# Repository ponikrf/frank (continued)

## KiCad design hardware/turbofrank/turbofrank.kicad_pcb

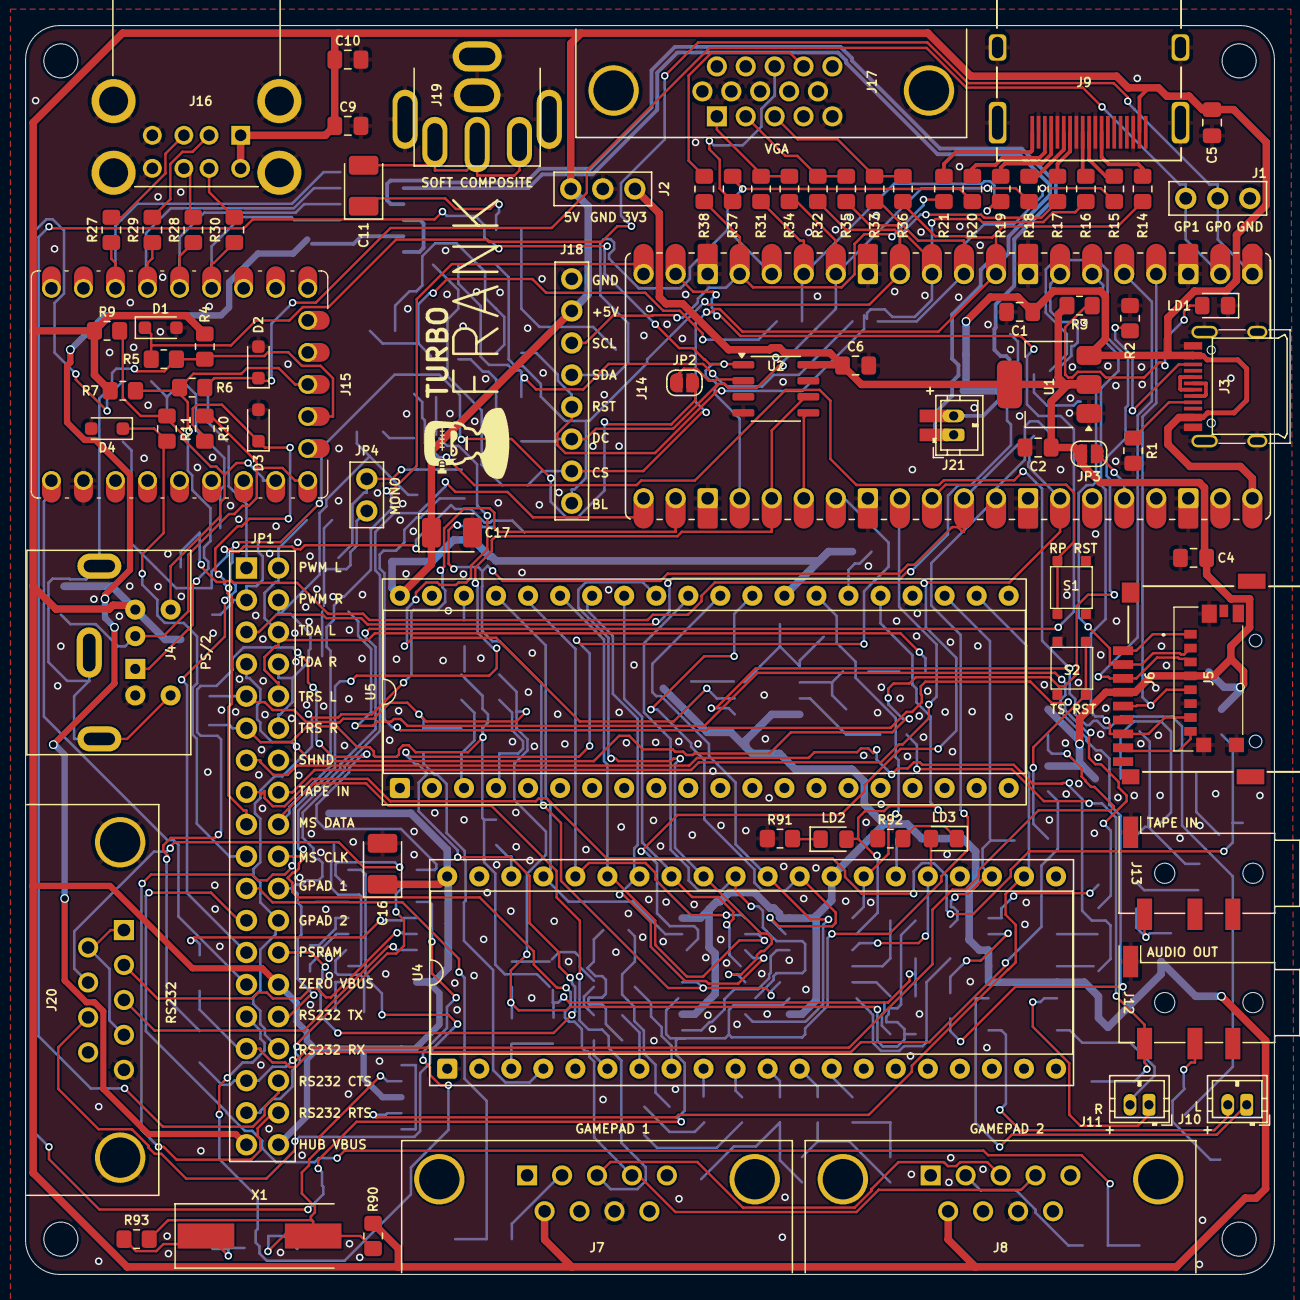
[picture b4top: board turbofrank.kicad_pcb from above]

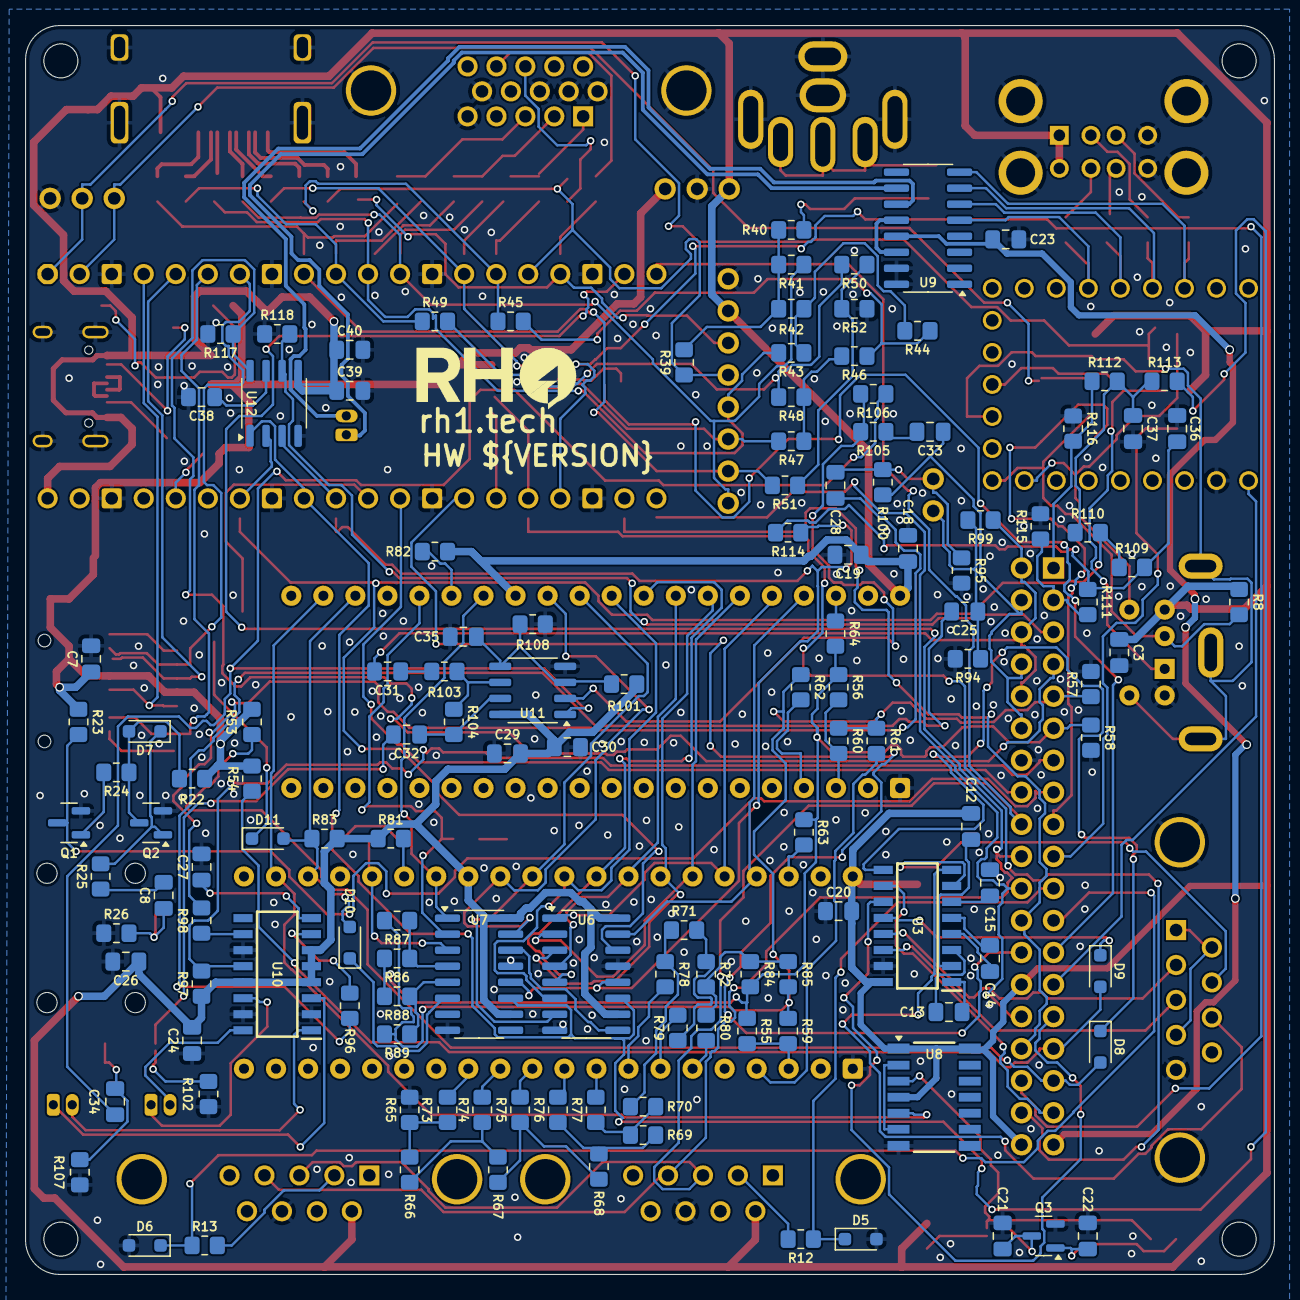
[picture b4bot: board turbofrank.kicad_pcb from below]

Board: 2 copper layers, 99.0 x 99.0 mm, 219 parts (132 on the bottom side), 187 nets.

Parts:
C1, C2, C9, C10, C29, C31, C32, C33, C34, C35, C38, C39: 10u; Capacitor (0805)
C3, C4, C5, C6, C7, C8, C18, C19, C20, C27, C30, C40: 100n; Capacitor (0805)
C11: 220u; Capacitor (3528, tantalum, polar)
C12, C13, C14, C15, C24, C25, C28: 1u; Capacitor (0805)
C16, C17: 100u; Capacitor (3528, tantalum, polar)
C21, C22: 22p; Capacitor (0805)
C23: 4.7u; Capacitor (0805)
C26: 47u; Capacitor (0805)
C36, C37: 47n; Capacitor (0805)
D1, D2, D3, D4, D5, D6: 3V3; Diode (SOD-323)
D7, D8, D9, D10, D11: 1N4148; Diode (SOD-323)
H1, H2, H3, H4: Hole 2.7mm; Mounting Hole (2.7mm)
J1: UART; Pin Header (1x03)
J2: PWR; Pin Header (1x03)
J3: USB4215; USB Type C
J4: MDC-036; MiniDIN (6 Pin, female)
J5: 0475710001; MicroSD (SMD, short)
J6: 104031-0811; MicroSD (SMD, long)
J7, J8, J20: D-SUB 9 Male; D-SUB (9 pin, male, top mount)
J9: DC3RX19JA2; HDMI (female)
J10: PAM L; Connector Female ZH 1.50mm (2 pins)
J11: PAM R; Connector Female ZH 1.50mm (2 pins)
J12, J13: PJ-320D; Jack (3.5mm, PJ-320D)
J14: Rasberry Pi Pico; Raspberry Pi Pico
J15: RP2040-Zero; Raspberry Pi Zero
J16: SS-52100-004; USB Type A (stacked)
J17: D-SUB 15 Female; D-SUB (15 pin, female)
J18: Pin Header 1x08; Pin Header (1x08)
J19: RCA-103; RCA
J21: USB HUB Data; Connector Female ZH 1.50mm (2 pins + tracks)
JP1: Main Jumper Set; Pin Header (2x19)
JP2, JP3: Jumper (Solder); Jumper (solder)
JP4: Mono; Pin Header (1x02)
LD1: Green; LED (0805)
LD2, LD3: Orange; LED (0805)
Q1, Q2, Q3: BC850; SOT-23
R1, R2: 5.1K; Resistor (0805)
R3, R4, R7, R8, R9, R12, R13, R23, R34, R35, R36, R53, R54, R66, R67, R68, R69, R70, R71, R72, R81, R82, R90, R91, R92, R113, R114: 1K; Resistor (0805)
R5, R6, R10, R11, R26, R37, R38: 100R; Resistor (0805)
R14, R15, R16, R17, R18, R19, R20, R21, R41, R43, R45, R47, R49, R51: 270R; Resistor (0805)
R22, R24, R25, R83, R84, R85, R86, R87, R88, R89, R96, R97, R98, R99, R100, R101, R103, R105, R108, R111, R112: 10K; Resistor (0805)
R27, R28, R29, R30: 22R; Resistor (0805)
R31, R32, R33: 330R; Resistor (0805)
R39: 750R; Resistor (0805)
R40: 51R; Resistor (0805)
R42, R44, R46, R48, R50: 150R; Resistor (0805)
R52: 300R; Resistor (0805)
R55, R56, R61, R62, R65, R73, R74, R75, R76, R77, R78, R79, R80, R94, R95, R109, R110, R115, R116: 2K; Resistor (0805)
R57, R58: 120R; Resistor (0805)
R59, R60, R63, R64: 4.7K; Resistor (0805)
R93: 100K; Resistor (0805)
R102, R107: 20K; Resistor (0805)
R104, R106: 47K; Resistor (0805)
R117, R118: 470R; Resistor (0805)
S1: TS-1233; Button (SMD, 3x3mm, 1-1)
S2: KLS7-TS3302; Button (SMD, 3x3mm, 1-1)
U1: NCP1117 3.3; SOT-223
U2: ESP-PSRAM32; SO-8
U3: MAX232CSE+; SOIC127P600X175-16N
U4, U5: JFC95101; DIP-40 (Socket)
U6, U7: 74HC595; SOP-16
U8: 74HC74; 74HCT74D
U9: MW7211A; SOP-16
U10: PAM8403D; SOIC127P600X175-16N
U11: LM358; SO-8
U12: TDA1387T; SO-8
X1: 3.58 MHz; Crystal (HC49-S)

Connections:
+3V3: C2.1, C4.2, C6.1, C7.1, J2.1, J5.P4 (VDD), J6.4 (VDD), JP3.2 (B), R3.2, R22.1, R23.1, R53.2, R54.2, U1.2 (VO), U2.8 (VCC)
/AMP_IN_L: C31.1, JP1.2, JP1.6, JP1.10, R99.1
/AMP_IN_R: C33.1, JP1.4, JP1.8, JP1.12, R100.1
/Audio Out/AMP_OUTL: C32.2, J12.T, R102.2
/Audio Out/AMP_OUTR: C34.2, J12.R, R107.2
/Audio Out/AMP_PAM_OUTL_M: J10.2, U10.3 (-OUTL)
/Audio Out/AMP_PAM_OUTL_P: J10.1, U10.1 (+OUT_L)
/Audio Out/AMP_PAM_OUTR_M: J11.2, U10.14 (-OUT_R)
/Audio Out/AMP_PAM_OUTR_P: J11.1, U10.16 (+OUT_R)
/Audio Out/Amplifier/ MONO_L: C25.1, JP4.1, R94.1, R99.2
/Audio Out/Amplifier/MONO_R: C28.1, JP4.2, R95.1, R100.2
/Audio Out/TS/A1: R62.2, U5.4 (B)
/Audio Out/TS/A2: R61.2, U4.4 (B)
/Audio Out/TS/B1: R56.2, R60.2, U5.3 (A)
/Audio Out/TS/B2: R55.2, R59.2, U4.3 (A)
/Audio Out/TS/BEEP: R86.2, R87.2, U7.4 (QE)
/Audio Out/TS/C1: R64.2, U5.38 (C)
/Audio Out/TS/C2: R63.2, U4.38 (C)
/Audio Out/TS/CLK_1.75M: U4.22 (CLOCK), U5.22 (CLOCK), U8.5 (Q)
/Audio Out/TS/COVOX_OUT: R72.2, R80.1, R84.2, R85.2
/Audio Out/TS/DA0: U4.37 (DA0), U5.37 (DA0), U6.15 (QA)
/Audio Out/TS/DA1: U4.36 (DA1), U5.36 (DA1), U6.1 (QB)
/Audio Out/TS/DA2: U4.35 (DA2), U5.35 (DA2), U6.2 (QC)
/Audio Out/TS/DA3: U4.34 (DA3), U5.34 (DA3), U6.3 (QD)
/Audio Out/TS/DA4: U4.33 (DA4), U5.33 (DA4), U6.4 (QE)
/Audio Out/TS/DA5: U4.32 (DA5), U5.32 (DA5), U6.5 (QF)
/Audio Out/TS/DA6: U4.31 (DA6), U5.31 (DA6), U6.6 (QG)
/Audio Out/TS/DA7: U4.30 (DA7), U5.30 (DA7), U6.7 (QH)
/Audio Out/TS/DAC0: R73.2, U4.13 (IOB0)
/Audio Out/TS/DAC1: R74.2, U4.12 (IOB1)
/Audio Out/TS/DAC2: R75.2, U4.11 (IOB2)
/Audio Out/TS/DAC3: R76.2, U4.10 (IOB3)
/Audio Out/TS/DAC4: R77.2, U4.9 (IOB4)
/Audio Out/TS/DAC5: R78.2, U4.8 (IOB5)
/Audio Out/TS/DAC6: R79.2, U4.7 (IOB6)
/Audio Out/TS/DAC7: R80.2, U4.6 (IOB7)
/Audio Out/TS/SAVE: R88.2, R89.2, U7.5 (QF)
/Audio Out/TS/YM_BC1: U4.29 (BC1), U5.29 (BC1), U7.15 (QA)
/Audio Out/TS/YM_BDIR: U4.27 (BDIR), U5.27 (BDIR), U7.1 (QB)
/Audio Out/TS/YM_CS1: LD2.2 (A), U5.25 (A8), U7.2 (QC)
/Audio Out/TS/YM_CS2: LD3.2 (A), U4.25 (A8), U7.3 (QD)
/Audio Out/TS/YM_RST: D10.2 (A), D11.2 (A), R83.1, U4.23 (~RESET), U5.23 (~RESET)
/Audio Out/TS/YM_SEL1: R82.2, U5.26 (~SEL)
/Audio Out/TS/YM_SEL2: R81.2, U4.26 (~SEL)
/Composite/CVBS: C11.2, J19.1
/GP1_DATA: D5.1 (K), JP1.21, R12.1
/GP2_DATA: D6.1 (K), JP1.23, R13.1
/GPIO0: D1.1 (K), J1.2, J14.1 (GPIO0), R5.2
/GPIO1: D2.1 (K), J1.3, J14.2 (GPIO1), R6.2
/GPIO2: J5.P5 (CLK), J6.5 (CLK), J14.4 (GPIO2)
/GPIO3: J5.P3 (CMD), J6.3 (CMD), J14.5 (GPIO3)
/GPIO4: J5.P7 (DAT0), J6.7 (DAT0), J14.6 (GPIO4)
/GPIO5: J5.P2 (CD/DAT3), J6.2 (DAT3/CD), J14.7 (GPIO5)
/GPIO6: J14.9 (GPIO6), J18.7, R14.2, R36.1, R51.1
/GPIO7: J14.10 (GPIO7), R15.2, R33.1, R49.1
/GPIO8: J14.11 (GPIO8), J18.5, R16.2, R35.1, R43.1
/GPIO9: J14.12 (GPIO9), J18.8, R17.2, R32.1, R41.1
/GPIO10: J14.14 (GPIO10), J18.6, R18.2, R34.1, R47.1
/GPIO11: J14.15 (GPIO11), R19.2, R31.1, R45.1
/GPIO12: J14.16 (GPIO12), J18.4, R20.2, R37.2, R39.1
/GPIO13: J14.17 (GPIO13), J18.3, R21.2, R38.2
/GPIO14: J7.4, J8.4, J14.19 (GPIO14), JP1.20
/GPIO15: J7.3, J8.3, J14.20 (GPIO15), JP1.18
/GPIO16: J14.21 (GPIO16), JP1.22, JP1.30
/GPIO17: J14.22 (GPIO17), JP1.24, JP1.32
/GPIO18: J14.24 (GPIO18), JP1.34, U2.1 (~CE)
/GPIO19: J14.25 (GPIO19), JP1.36, U2.6 (SCLK)
/GPIO20: J14.26 (GPIO20), U2.5 (SI/SIO)
/GPIO21: J14.27 (GPIO21), JP1.26
/GPIO22: J14.29 (GPIO22), JP1.16
/GPIO26: J14.31 (GPIO26_ADC0), R114.2, U6.12 (RCLK), U7.12 (RCLK), U12.3 (DATA)
/GPIO27: J14.32 (GPIO27_ADC1), R113.2, U6.11 (SRCLK), U7.11 (SRCLK), U12.1 (SCLK)
/GPIO28: J14.34 (GPIO28_ADC2), R109.1, R110.1, U6.14 (SER), U12.2 (LRCK)
/KB_CLK: J4.5, J15.13 (12), R4.2, R5.1
/KB_DATA: J4.1, J15.12 (11), R6.1, R7.2
/LOAD_IN_D: JP1.15, Q1.3 (C), R23.2
/MS_CLK: J4.6, J15.16 (15), R9.2, R11.1
/MS_CLK_3V: D4.1 (K), JP1.19, R11.2
/MS_DATA: J4.2, J15.15 (14), R8.2, R10.1
/MS_DATA_3V: D3.1 (K), JP1.17, R10.2
/Micro SD/DAT1: J5.P8 (DAT1), J6.8 (DAT1)
/Micro SD/DAT2: J5.P1 (DAT2), J6.1 (DAT2)
/PSR_SOSIO: JP1.25, JP2.2 (B)
/PWM_OUT_L: JP1.1, R112.2, R116.1
/PWM_OUT_R: JP1.3, R111.2, R115.1
/Power/D+: J3.6 (DP1), J3.8 (DP2)
/Power/D-: J3.5 (DN2), J3.7 (DN1)
/RS232/C1+: C13.2, U3.1 (C1+)
/RS232/C1-: C13.1, U3.3 (C1-)
/RS232/C2+: C14.2, U3.4 (C2+)
/RS232/C2-: C14.1, U3.5 (C2-)
/RS232/CTS_IN: J20.7, U3.7 (T2OUT)
/RS232/CTS_MAX: D8.1 (K), U3.9 (R2OUT)
/RS232/RTS_IN: J20.8, U3.8 (R2IN)
/RS232/RX_IN: J20.3, U3.14 (T1OUT)
/RS232/RX_MAX: D9.1 (K), U3.12 (R1OUT)
/RS232/TX_IN: J20.2, U3.13 (R1IN)
/RS232/V+: C12.1, U3.2 (V+)
/RS232/V-: C15.1, U3.6 (V-)
/RS232_CTS: D8.2 (A), JP1.33, R53.1
/RS232_RTS: JP1.35, U3.10 (T2IN)
/RS232_RX: D9.2 (A), JP1.31, R54.1
/RS232_TX: JP1.29, U3.11 (T1IN)
/RUN: J14.30 (RUN), S1.1
/SHND: JP1.13, R97.2, U10.12 (SHND)
/TDA_L: JP1.5, R118.2, U12.6 (A_LEFT)
/TDA_R: JP1.7, R117.1, U12.8 (A_RIGHT)
/TS_L: JP1.9, R57.1, R59.1, R60.1, R61.1, R62.1, R85.1, R87.1, R89.1
/TS_R: JP1.11, R55.1, R56.1, R58.1, R63.1, R64.1, R84.1, R86.1, R88.1
/USB Hub/DM_IN: J21.2, U9.10 (DMU)
/USB Hub/DP_IN: J21.1, U9.11 (DPU)
/USBH_VBUS: C23.1, JP1.37, U9.13 (VDD5)
/USB_D1M: J15.4 (3), R29.1, U9.7 (DM3)
/USB_D1P: J15.3 (2), R27.1, U9.8 (DP3)
/USB_D2M: J15.6 (5), R30.1, U9.5 (DM2)
/USB_D2P: J15.5 (4), R28.1, U9.6 (DP2)
/ZERO_VBUS: J15.23 (5V), JP1.27
GND: C1.2, C2.2, C3.2, C4.1, C5.2, C6.2, C7.2, C9.2, C10.2, C15.2, C16.2, C17.2, C18.2, C19.2, C20.2, C21.1, C22.1, C23.2, C24.2, C26.2, C27.2, C29.1, C30.1, C35.1, C36.2, C37.2, C38.2, C39.2, C40.2, D1.2 (A), D2.2 (A), D3.2 (A), D4.2 (A), D5.2 (A), D6.2 (A), J1.1, J2.2, J3.1 (GND), J3.12 (GND), J3.13 (SHIELD), J4.3, J5.G1 (GND_1), J5.G2 (GND_2), J5.G3 (GND_3), J5.P6 (VSS), J6.6 (VSS), J7.8, J8.8, J9.2 (G_D2), J9.5 (G_D1), J9.8 (G_D0), J9.11 (G_CLK), J9.17 (G_DDC/CEC), J9.20 (SHIELD1), J9.21 (SHIELD2), J9.22 (SHIELD3), J9.23 (SHIELD4), J12.S, J13.S, J14.3 (GND), J14.8 (GND), J14.13 (GND), J14.18 (GND), J14.23 (GND), J14.28 (GND), J14.33 (AGND), J14.38 (GND), J15.22 (GND), J16.4 (GND1), J16.8 (GND2), J16.9 (Shield), J17.0, J17.5, J17.6, J17.7, J17.8, J17.10, J18.1, J19.2, J20.5, JP1.14, LD1.1 (K), Q1.2 (E), Q2.2 (E), Q3.2 (E), R1.1, R2.1, R26.2, R52.1, R57.2, R58.2, R65.1, R91.1, R92.1, R94.2, R95.2, R102.1, R107.1, R108.1, R115.2, R116.2, R117.2, R118.1, S1.2, S2.2, U1.1 (GND), U2.4 (VSS), U3.15 (GND), U4.1 (VSS), U4.24 (~A9), U5.1 (VSS), U5.24 (~A9), U6.8 (GND), U6.13 (~OE), U7.8 (GND), U7.13 (~OE), U8.7 (GND), U9.15 (GND), U9.16 (GND), U10.2 (PGND), U10.11 (GND), U10.15 (PGND), U11.4 (V-), U12.4 (AGND)
unnamed: C8.1, J13.T, R26.1
unnamed: C8.2, R25.1
unnamed: C11.1, R40.2
unnamed: C25.2, R96.2
unnamed: C28.2, R98.2
unnamed: C31.2, R103.2
unnamed: C32.1, R104.1, U11.7
unnamed: C33.2, R105.2
unnamed: C34.1, R106.1, U11.1
unnamed: C36.1, R109.2, R111.1, R114.1
unnamed: C37.1, R110.2, R112.1, R113.1
unnamed: D7.2 (A), Q2.3 (C), R22.2, R24.1
unnamed: D7.1 (K), Q2.1 (B), R25.2
unnamed: D10.1 (K), U7.6 (QG)
unnamed: D11.1 (K), S2.1
unnamed: J3.4 (CC1), R1.2
unnamed: J3.10 (CC2), R2.2
unnamed: J7.2, R12.2
unnamed: J8.2, R13.2
unnamed: J9.12 (CLKN), R14.1
unnamed: J9.10 (CLKP), R15.1
unnamed: J9.9 (D0N), R16.1
unnamed: J9.7 (D0P), R17.1
unnamed: J9.6 (D1N), R18.1
unnamed: J9.4 (D1P), R19.1
unnamed: J9.3 (D2N), R20.1
unnamed: J9.1 (D2P), R21.1
unnamed: J14.36 (3V3), JP3.1 (A)
unnamed: J16.3 (D1+), R27.2
unnamed: J16.2 (D1-), R29.2
unnamed: J16.7 (D2+), R28.2
unnamed: J16.6 (D2-), R30.2
unnamed: J17.1, R31.2, R34.2
unnamed: J17.2, R32.2, R35.2
unnamed: J17.3, R33.2, R36.2
unnamed: J17.13, R37.1
unnamed: J17.14, R38.1
unnamed: J20.1, J20.4, J20.6
unnamed: JP2.1 (A), U2.2 (SO/SIO)
unnamed: LD1.2 (A), R3.1
unnamed: LD2.1 (K), R91.2
unnamed: LD3.1 (K), R92.2
unnamed: Q1.1 (B), R24.2
unnamed: C22.2, Q3.1 (B), R93.1, X1.1
unnamed: C21.2, Q3.3 (C), R90.1, R93.2, U8.3 (C), X1.2
unnamed: R39.2, R40.1, R41.2, R42.2
unnamed: R42.1, R43.2, R44.2
unnamed: R44.1, R45.2, R46.2
unnamed: R46.1, R47.2, R48.2
unnamed: R48.1, R49.2, R50.2
unnamed: R50.1, R51.2, R52.2
unnamed: R65.2, R66.1, R73.1
unnamed: R66.2, R67.1, R74.1
unnamed: R67.2, R68.1, R75.1
unnamed: R68.2, R69.1, R76.1
unnamed: R69.2, R70.1, R77.1
unnamed: R70.2, R71.1, R78.1
unnamed: R71.2, R72.1, R79.1
unnamed: U6.9 (QH'), U7.14 (SER)
unnamed: U8.2 (D), U8.6 (~Q)
unnamed: U9.12 (VD33), U9.14 (VD3)
unnamed: R96.1, U10.7 (INL)
unnamed: R98.1, U10.10 (INR)
unnamed: C27.1, U10.8 (VREF)
unnamed: C35.2, R101.1, R108.2, U11.3 (+), U11.5 (+)
unnamed: R105.1, R106.2, U11.2 (-)
unnamed: R103.1, R104.2, U11.6 (-)
unnamed: C38.1, U12.7 (FLT)
VBUS: C1.1, C3.1, C5.1, C9.1, C10.1, C12.2, C16.1, C17.1, C18.1, C19.1, C20.1, C24.1, C26.1, C29.2, C30.2, C39.1, C40.1, J2.3, J3.2 (VBUS), J3.11 (VBUS), J4.4, J7.6, J8.6, J9.18 (+5V), J14.40 (VBUS), J16.1 (VBUS1), J16.5 (VBUS2), J18.2, JP1.28, JP1.38, R4.1, R7.1, R8.1, R9.1, R81.1, R82.1, R83.2, R90.2, R97.1, R101.2, U1.3 (VI), U3.16 (VCC), U4.28 (BC2), U4.40 (VCC), U5.28 (BC2), U5.40 (VCC), U6.10 (~SRCLR), U6.16 (VCC), U7.10 (~SRCLR), U7.16 (VCC), U8.1 (~R), U8.4 (~S), U8.14 (VCC), U10.4 (PVDD), U10.5 (MUTE), U10.6 (VDD), U10.13 (PVDD), U11.8 (V+), U12.5 (VA)

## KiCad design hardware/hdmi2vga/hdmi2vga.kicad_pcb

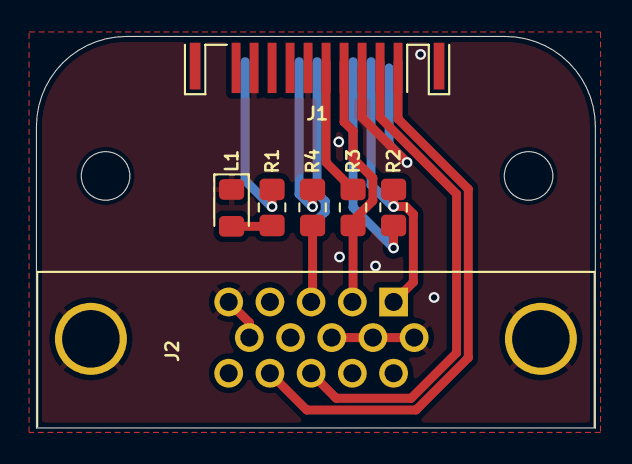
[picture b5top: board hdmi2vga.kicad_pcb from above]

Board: 2 copper layers, 31.1 x 21.8 mm, 9 parts (0 on the bottom side), 11 nets.

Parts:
H1, H2: MountingHole; Mounting Hole (2.7mm)
J1: HDMI; HDMI (male)
J2: VGA; D-SUB (15 pin, female)
L1: HDMI LED; LED (0805)
R1: 1K; Resistor (0805)
R2, R3, R4: 820R; Resistor (0805)

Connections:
/CLKN_VGA_B: J1.12 (CLKN), R4.1
/CLKP_VGA_BH: J1.10 (CLKP), J2.3, R4.2
/D0N_VGA_G: J1.9 (D0N), R3.1
/D0P_VGA_GH: J1.7 (D0P), J2.2, R3.2
/D1N_VGA_R: J1.6 (D1N), R2.1
/D1P_VGA_RH: J1.4 (D1P), J2.1, R2.2
/D2N_VGA_HS: J1.3 (D2N), J2.13
/D2P_VGA_VS: J1.1 (D2P), J2.14
GND: J1.2 (G_D2), J1.5 (G_D1), J1.8 (G_D0), J1.11 (G_CLK), J1.17 (G_DDC/CEC), J2.0, J2.5, J2.6, J2.7, J2.8, J2.10, L1.1 (K)
unnamed: J1.18 (+5V), R1.1
unnamed: L1.2 (A), R1.2

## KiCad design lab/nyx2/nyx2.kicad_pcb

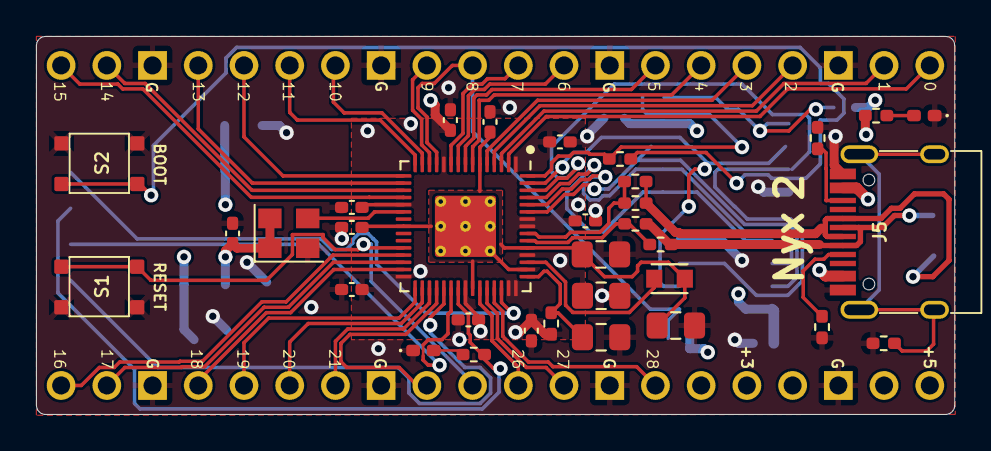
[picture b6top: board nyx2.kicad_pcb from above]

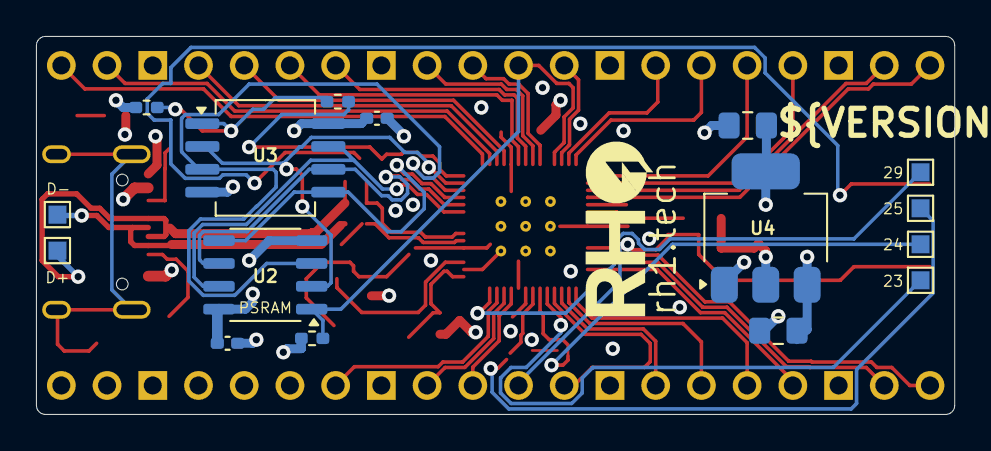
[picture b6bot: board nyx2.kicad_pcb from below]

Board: 4 copper layers, 51.0 x 21.0 mm, 47 parts (12 on the bottom side), 55 nets.

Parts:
C1, C3, C4, C5, C6, C7, C8, C9, C10, C11, C15, C16: 100n; Capacitor (0402)
C2, C12, C13, C14: 4.7u; Capacitor (0805)
C17, C18: 10u; Capacitor (0805)
J1: CON_PICO_21-40
J2: CON_PICO_1-20
J3: Test Points (1mm x 5)
J4: Test Points (1mm x 2)
J5: USB4215-03-A; USB Type C
L1: 3.3u; IND_LQH2MCN100K02L
LD1: Blue; LED (0402)
LD2: Green; LED (0402)
R1, R4: 150R; Resistor (0402)
R2: 33; Resistor (0402)
R3, R5: 33R; Resistor (0402)
R6, R10, R12: 1K; Resistor (0402)
R7, R8: 10K; Resistor (0402)
R9: 0R; Resistor (0402)
R11, R13: 5.1K; Resistor (0402)
R14: 1M; Resistor (0402)
S1: Reset; Button (SMD, 3x3mm, 1-1)
S2: TS-1233; Button (SMD, 3x3mm, 1-1)
U1: RP2350; QFN 60 (RP2350A)
U2: ESP-PSRAM32; SO-8
U3: W25Q128JVS; SOIC-8
U4: NCP1117 3.3; SOT-223
Y1: ASE-12MHz; Crystal (3225, active)

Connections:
+1V1: C1.1, C2.1, C3.1, C14.1, L1.1, U1.6 (DVDD), U1.23 (DVDD), U1.39 (DVDD), U1.50 (VREG_FB)
+3V3: C4.1, C5.1, C6.1, C7.1, C8.1, C9.1, C10.1, C11.1, C13.1, C15.1, C16.1, C18.1, J1.36, R2.1, R7.2, R8.1, R12.2, U1.1 (IOVDD), U1.11 (IOVDD), U1.20 (IOVDD), U1.30 (IOVDD), U1.38 (IOVDD), U1.44 (ADC_AVDD), U1.45 (IOVDD), U1.49 (VREG_VIN), U1.53 (USB_OTP_VDD), U1.54 (QSPI_IOVDD), U2.8 (VCC), U3.8 (VCC), U4.2 (VO), Y1.1 (EN), Y1.4 (Vdd)
/D+: J4.1, J5.6 (DP1), J5.8 (DP2), R1.1, R3.1
/D-: J4.2, J5.5 (DN2), J5.7 (DN1), R4.1, R5.1
/GPIO0: J2.1, U1.2 (GPIO0)
/GPIO1: J2.2, U1.3 (GPIO1)
/GPIO2: J2.4, U1.4 (GPIO2)
/GPIO3: J2.5, U1.5 (GPIO3)
/GPIO4: J2.6, U1.7 (GPIO4)
/GPIO5: J2.7, U1.8 (GPIO5)
/GPIO6: J2.9, U1.9 (GPIO6)
/GPIO7: J2.10, U1.10 (GPIO7)
/GPIO8: J2.11, R7.1, U1.12 (GPIO8), U2.1 (~CE)
/GPIO9: J2.12, U1.13 (GPIO9)
/GPIO10: J2.14, U1.14 (GPIO10)
/GPIO11: J2.15, U1.15 (GPIO11)
/GPIO12: J2.16, U1.16 (GPIO12)
/GPIO13: J2.17, U1.17 (GPIO13)
/GPIO14: J2.19, U1.18 (GPIO14)
/GPIO15: J2.20, U1.19 (GPIO15)
/GPIO16: J1.21, U1.27 (GPIO16)
/GPIO17: J1.22, U1.28 (GPIO17)
/GPIO18: J1.24, U1.29 (GPIO18)
/GPIO19: J1.25, U1.31 (GPIO19)
/GPIO20: J1.26, U1.32 (GPIO20)
/GPIO21: J1.27, U1.33 (GPIO21)
/GPIO22: J1.29, U1.34 (GPIO22)
/GPIO23: J3.1, U1.35 (GPIO23)
/GPIO24: J3.2, U1.36 (GPIO24)
/GPIO26: J1.31, U1.40 (GPIO26_ADC0)
/GPIO27: J1.32, U1.41 (GPIO27_ADC1)
/GPIO28: J1.34, U1.42 (GPIO28_ADC2)
/GPIO29: J3.4, U1.43 (GPIO29_ADC3)
/RP2350A/FLASH_SS: R8.2, R9.2, U3.1 (~CS)
/RP2350A/QSPI_SCLK: U1.56 (QSPI_SCLK), U2.6 (SCLK), U3.6 (CLK)
/RP2350A/QSPI_SD0: U1.57 (QSPI_SD0), U2.5 (SI/SIO), U3.5 (DI(IO0))
/RP2350A/QSPI_SD1: U1.59 (QSPI_SD1), U2.2 (SO/SIO), U3.2 (DO(IO1))
/RP2350A/QSPI_SD2: U1.58 (QSPI_SD2), U2.3 (SIO2), U3.3 (IO2)
/RP2350A/QSPI_SD3: U1.55 (QSPI_SD3), U2.7 (SIO3), U3.7 (IO3)
/RP2350A/QSPI_SS: R6.1, R9.1, U1.60 (QSPI_SS)
/RP2350A/VREG_AVDD: C12.1, R2.2, U1.46 (VREG_AVDD)
/RP2350A/VREG_LX: L1.2, U1.48 (VREG_LX)
/RP2350A/XIN: U1.21 (XIN), Y1.3 (OUT)
/RP2350A/~USB_BOOT: R6.2, S2.2
/RUN: J1.30, S1.1, U1.26 (RUN)
GND: C1.2, C2.2, C3.2, C4.2, C5.2, C6.2, C7.2, C8.2, C9.2, C10.2, C11.2, C12.2, C13.2, C14.2, C15.2, C16.2, C17.2, C18.2, J1.23, J1.28, J1.33, J1.38, J2.3, J2.8, J2.13, J2.18, J5.1 (GND), J5.12 (GND), LD1.1 (K), LD2.1 (K), R11.1, R13.1, R14.2, S1.2, S2.1, U1.47 (VREG_PGND), U1.61 (GND), U2.4 (VSS), U3.4 (GND), U4.1 (GND), Y1.2 (GND)
GPIO25: J3.3, R10.2, U1.37 (GPIO25)
unnamed: J5.4 (CC1), R11.2
unnamed: J5.10 (CC2), R13.2
unnamed: J5.13 (SHIELD), R14.1
unnamed: LD1.2 (A), R10.1
unnamed: LD2.2 (A), R12.1
unnamed: R4.2, R5.2, U1.51 (USB_DM)
unnamed: R1.2, R3.2, U1.52 (USB_DP)
VBUS: C17.1, J1.40, J5.2 (VBUS), J5.11 (VBUS), U4.3 (VI)

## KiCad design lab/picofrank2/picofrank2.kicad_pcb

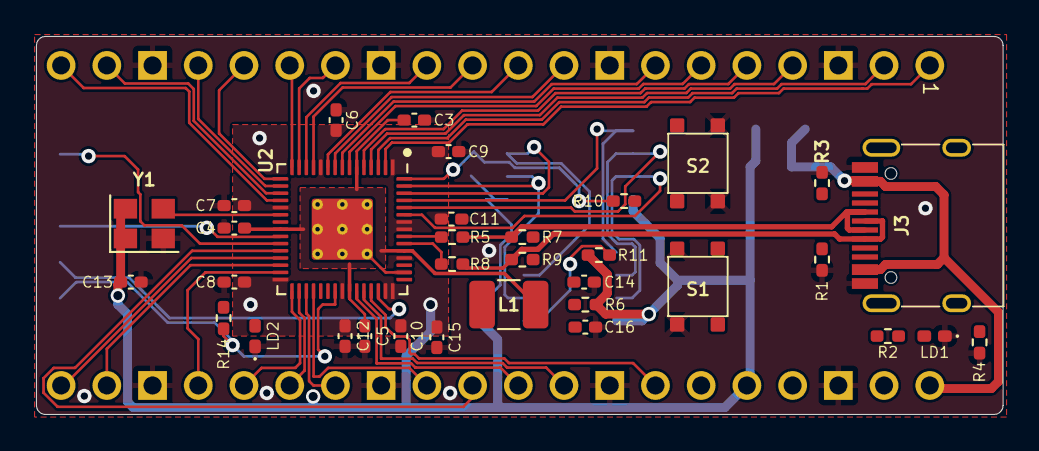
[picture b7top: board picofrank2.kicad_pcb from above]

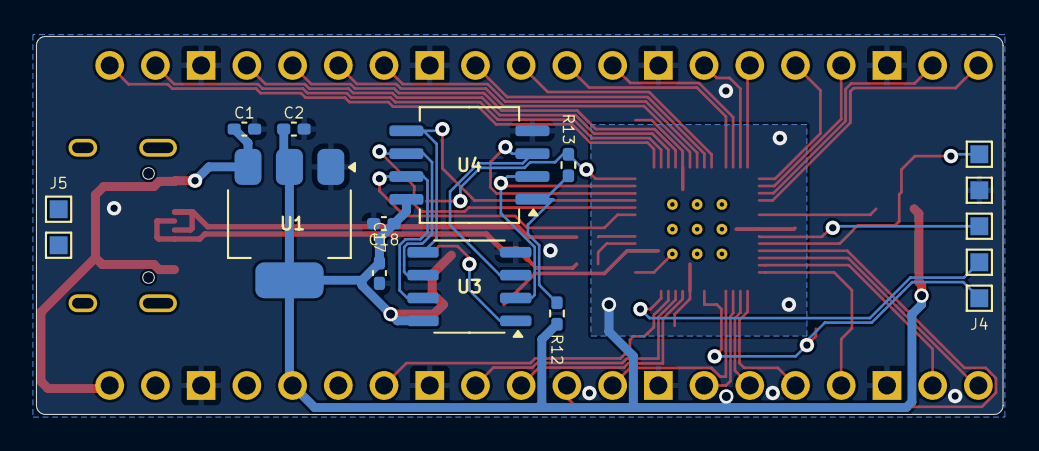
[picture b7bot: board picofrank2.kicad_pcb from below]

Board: 2 copper layers, 53.7 x 21.0 mm, 47 parts (11 on the bottom side), 55 nets.

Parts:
C1, C2: 10u; Capacitor (0402)
C3, C5, C6, C7, C8, C9, C10, C11, C12, C13, C17, C18: 100n; Capacitor (0402)
C4, C14, C15, C16: 4.7u; Capacitor (0402)
J1: CON_PICO_21-40
J2: CON_PICO_1-20
J3: USB4215-03-A; USB Type C
J4: Test Points (1mm x 5)
J5: Test Points (1mm x 2)
L1: 3.3u; Inductor (3225)
LD1: Green; LED (0402)
LD2: Blue; LED (0402)
R1, R3: 5.1K; Resistor (0402)
R2, R10, R14: 1K; Resistor (0402)
R4: 1M; Resistor (0402)
R5, R8: 150R; Resistor (0402)
R6: 33; Resistor (0402)
R7, R9: 33R; Resistor (0402)
R11, R12: 10K; Resistor (0402)
R13: 0; Resistor (0402)
S1: Reset; Button (SMD, 3x3mm, 1-1)
S2: TS-1233; Button (SMD, 3x3mm, 1-1)
U1: NCP1117 3.3; SOT-223
U2: RP2350; QFN 60 (RP2350A)
U3: ESP-PSRAM32; SO-8
U4: W25Q128JVS; SOIC-8
Y1: ASE-12MHz; Crystal (3225, active)

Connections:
+1V1: C3.1, C4.1, C5.1, C16.1, L1.1, U2.6 (DVDD), U2.23 (DVDD), U2.39 (DVDD), U2.50 (VREG_FB)
+3V3: C2.1, C6.1, C7.1, C8.1, C9.1, C10.1, C11.1, C12.1, C13.1, C15.1, C17.1, C18.1, J1.36, R2.2, R6.1, R11.2, R12.1, U1.2 (VO), U2.1 (IOVDD), U2.11 (IOVDD), U2.20 (IOVDD), U2.30 (IOVDD), U2.38 (IOVDD), U2.44 (ADC_AVDD), U2.45 (IOVDD), U2.49 (VREG_VIN), U2.53 (USB_OTP_VDD), U2.54 (QSPI_IOVDD), U3.8 (VCC), U4.8 (VCC), Y1.1 (EN), Y1.4 (Vdd)
/D+: J3.6 (DP1), J3.8 (DP2), J5.1, R5.1, R7.1
/D-: J3.5 (DN2), J3.7 (DN1), J5.2, R8.1, R9.1
/GPIO0: J2.1, U2.2 (GPIO0)
/GPIO1: J2.2, U2.3 (GPIO1)
/GPIO2: J2.4, U2.4 (GPIO2)
/GPIO3: J2.5, U2.5 (GPIO3)
/GPIO4: J2.6, U2.7 (GPIO4)
/GPIO5: J2.7, U2.8 (GPIO5)
/GPIO6: J2.9, U2.9 (GPIO6)
/GPIO7: J2.10, U2.10 (GPIO7)
/GPIO8: J2.11, R11.1, U2.12 (GPIO8), U3.1 (~CE)
/GPIO9: J2.12, U2.13 (GPIO9)
/GPIO10: J2.14, U2.14 (GPIO10)
/GPIO11: J2.15, U2.15 (GPIO11)
/GPIO12: J2.16, U2.16 (GPIO12)
/GPIO13: J2.17, U2.17 (GPIO13)
/GPIO14: J2.19, U2.18 (GPIO14)
/GPIO15: J2.20, U2.19 (GPIO15)
/GPIO16: J1.21, U2.27 (GPIO16)
/GPIO17: J1.22, U2.28 (GPIO17)
/GPIO18: J1.24, U2.29 (GPIO18)
/GPIO19: J1.25, U2.31 (GPIO19)
/GPIO20: J1.26, U2.32 (GPIO20)
/GPIO21: J1.27, U2.33 (GPIO21)
/GPIO22: J1.29, U2.34 (GPIO22)
/GPIO26: J1.31, U2.40 (GPIO26_ADC0)
/GPIO27: J1.32, U2.41 (GPIO27_ADC1)
/GPIO28: J1.34, U2.42 (GPIO28_ADC2)
/GPIO29: J4.2, U2.43 (GPIO29_ADC3)
/RP2350A/FLASH_SS: R12.2, R13.2, U4.1 (~CS)
/RP2350A/QSPI_SCLK: U2.56 (QSPI_SCLK), U3.6 (SCLK), U4.6 (CLK)
/RP2350A/QSPI_SD0: U2.57 (QSPI_SD0), U3.5 (SI/SIO), U4.5 (DI(IO0))
/RP2350A/QSPI_SD1: U2.59 (QSPI_SD1), U3.2 (SO/SIO), U4.2 (DO(IO1))
/RP2350A/QSPI_SD2: U2.58 (QSPI_SD2), U3.3 (SIO2), U4.3 (IO2)
/RP2350A/QSPI_SD3: U2.55 (QSPI_SD3), U3.7 (SIO3), U4.7 (IO3)
/RP2350A/QSPI_SS: R10.1, R13.1, U2.60 (QSPI_SS)
/RP2350A/VREG_AVDD: C14.1, R6.2, U2.46 (VREG_AVDD)
/RP2350A/VREG_LX: L1.2, U2.48 (VREG_LX)
/RP2350A/XIN: U2.21 (XIN), Y1.3 (OUT)
/RP2350A/~USB_BOOT: R10.2, S2.2
/RUN: J1.30, S1.1, U2.26 (RUN)
/SWCLK: J4.3, U2.24 (SWCLK)
/SWD: J4.5, U2.25 (SWD)
GND: C1.2, C2.2, C3.2, C4.2, C5.2, C6.2, C7.2, C8.2, C9.2, C10.2, C11.2, C12.2, C13.2, C14.2, C15.2, C16.2, C17.2, C18.2, J1.23, J1.28, J1.33, J1.38, J2.3, J2.8, J2.13, J2.18, J3.1 (GND), J3.12 (GND), J4.4, LD1.1 (K), LD2.1 (K), R1.1, R3.1, R4.2, S1.2, S2.1, U1.1 (GND), U2.47 (VREG_PGND), U2.61 (GND), U3.4 (VSS), U4.4 (GND), Y1.2 (GND)
GPIO25: J4.1, R14.2, U2.37 (GPIO25)
unnamed: J3.4 (CC1), R1.2
unnamed: J3.10 (CC2), R3.2
unnamed: J3.13 (SHIELD), R4.1
unnamed: LD1.2 (A), R2.1
unnamed: LD2.2 (A), R14.1
unnamed: R8.2, R9.2, U2.51 (USB_DM)
unnamed: R5.2, R7.2, U2.52 (USB_DP)
VBUS: C1.1, J1.40, J3.2 (VBUS), J3.11 (VBUS), U1.3 (VI)

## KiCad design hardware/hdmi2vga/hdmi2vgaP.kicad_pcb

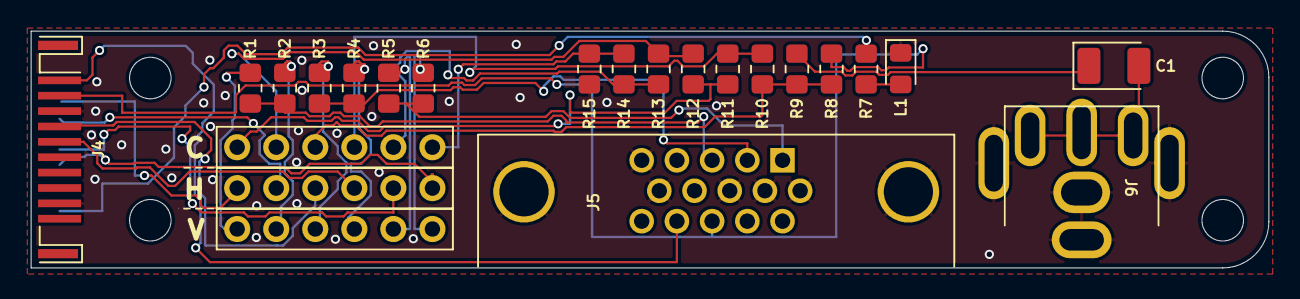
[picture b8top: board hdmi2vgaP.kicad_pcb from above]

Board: 2 copper layers, 80.5 x 15.4 mm, 27 parts (0 on the bottom side), 28 nets.

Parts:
C1: 220u; Capacitor (3528, tantalum, polar)
H1, H2, H3, H4: MountingHole; Mounting Hole (2.7mm)
J1: HDMI; Pin Header (1x06)
J2: VGA; Pin Header (1x06)
J3: Composite; Pin Header (1x06)
J4: HDMI; HDMI (male)
J5: VGA; D-SUB (15 pin, female)
J6: VIDEO (Soft Composite); RCA
L1: HDMI LED; LED (0805)
R1, R3, R5: 820R; Resistor (0805)
R2, R4, R6: 0R; Resistor (0805)
R7: 1K; Resistor (0805)
R8: 510R; Resistor (0805)
R9: 51R*; Resistor (0805)
R10, R11, R12, R13, R14: 150R; Resistor (0805)
R15: 300R; Resistor (0805)

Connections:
/HDMI/CLKN: J1.1, J4.12 (CLKN)
/HDMI/CLKP: J1.2, J4.10 (CLKP)
/HDMI/D0N: J1.3, J4.9 (D0N)
/HDMI/D0P: J1.4, J4.7 (D0P)
/HDMI/D1N: J1.5, J4.6 (D1N)
/HDMI/D1P: J1.6, J4.4 (D1P)
/HDMI/D2N: J4.3 (D2N), J5.13, R8.1
/HDMI/D2P: J4.1 (D2P), J5.14
/HDMI/VBUS: J4.18 (+5V), R7.1
/Soft Composite/CLKN: J3.1, R14.1, R15.2
/Soft Composite/CLKP: J3.2, R13.1, R14.2
/Soft Composite/CVBS: C1.2, J6.1
/Soft Composite/D0N: J3.3, R10.1, R11.2
/Soft Composite/D0P: J3.4, R8.2, R9.1, R10.2
/Soft Composite/D1N: J3.5, R12.1, R13.2
/Soft Composite/D1P: J3.6, R11.1, R12.2
/VGA/VGA_BH: J5.3, R1.2, R2.2
/VGA/VGA_GH: J5.2, R3.2, R4.2
/VGA/VGA_RH: J5.1, R5.2, R6.2
GND: J4.2 (G_D2), J4.5 (G_D1), J4.8 (G_D0), J4.11 (G_CLK), J4.17 (G_DDC/CEC), J5.0, J5.5, J5.6, J5.7, J5.8, J5.10, J6.2, L1.1 (K), R15.1
unnamed: C1.1, R9.2
unnamed: J2.1, R1.1
unnamed: J2.2, R2.1
unnamed: J2.3, R3.1
unnamed: J2.4, R4.1
unnamed: J2.5, R5.1
unnamed: J2.6, R6.1
unnamed: L1.2 (A), R7.2

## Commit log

2025-03-16 Bugfixes
2025-03-16 TurboFRANK HW 1.03
2025-03-16 Moved WIP to lab
2025-03-16 Fixed tape loading bug on all PCBs
2025-03-17 TurboFRANK 1.04 WIP
2025-03-18 TurboFRANK HW 1.04 WIP
2025-03-19 TurboFRANK HW 1.04 (release)
2025-03-24 RM1E WIP
2025-03-24 MiniFRANK RM1E HW 1.00
2025-03-26 FRANK M1 1.16 WIP
2025-03-26 FRANK M1 1.16
2025-04-01 Minor updates
2025-04-01 MiniFRANK RM1 2.03
2025-04-03 Fixes
2025-04-04 TurboFRANK WIP
2025-04-04 TurboFrank HW
2025-04-05 TurboFRANK 1.05 HW
2025-04-05 TurboFRANK HW 1.05 Release
2025-04-07 MiniFRANK RM1 WIP
2025-04-07 MiniFRANK 2.05 Release
2025-04-07 Cleanup
2025-04-08 RM24 WIP
2025-04-09 FRANK M1 1.17
2025-04-09 MiniFRANK RM24 1.01
2025-04-09 Added missing 3D models for Protea
2025-04-15 Minor fixes
2025-04-16 PicoFRANK2 WIP
2025-04-16 Experimental boards added
2025-04-24 MiniFRANK RM1 2.07
2025-04-24 MiniFRANK RM1e archived
2025-05-01 TurboFRANK HW 1.07
2025-05-06 Nyx2 HW 1.03
2025-05-07 Protea is not a part of FRANK anymore
2025-05-07 Revision 2.03
2025-05-11 MiniFRANK RM2 WIP
2025-05-11 MiniFRANK RM2 1.02
2025-05-11 MiniFRANK RM1 2.07: Minor Updates
2025-05-22 Улучшения разводки
    Некоторые простые компоненты - например сопротивления и конденсаторы были выровнены. Другие компоненты свое положение не меняли. Улучшена общая компоновка проводников, которая лучше использует свобод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
